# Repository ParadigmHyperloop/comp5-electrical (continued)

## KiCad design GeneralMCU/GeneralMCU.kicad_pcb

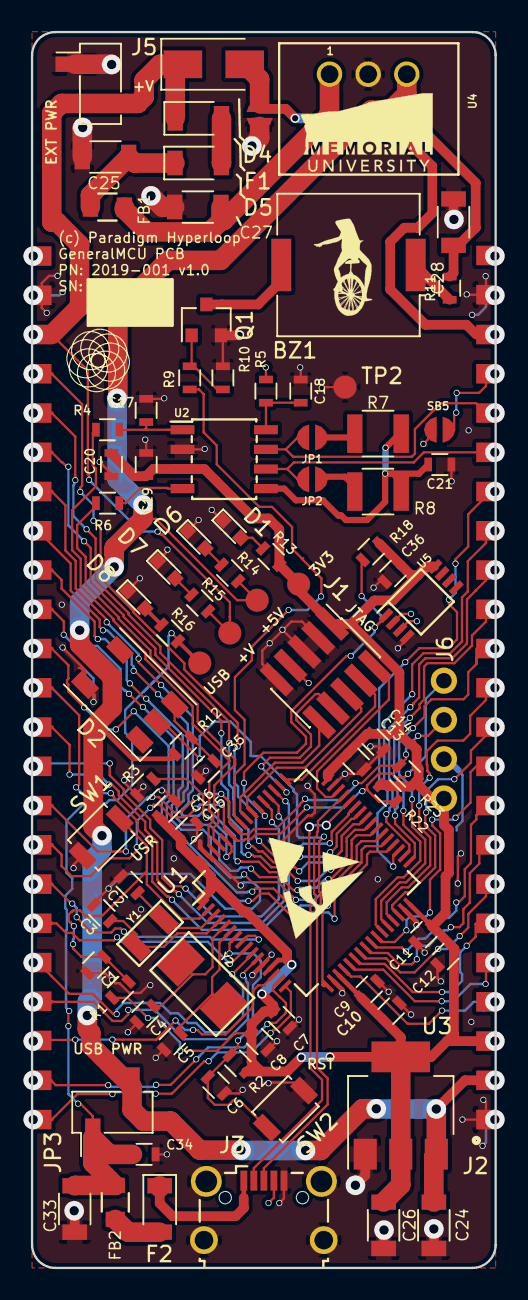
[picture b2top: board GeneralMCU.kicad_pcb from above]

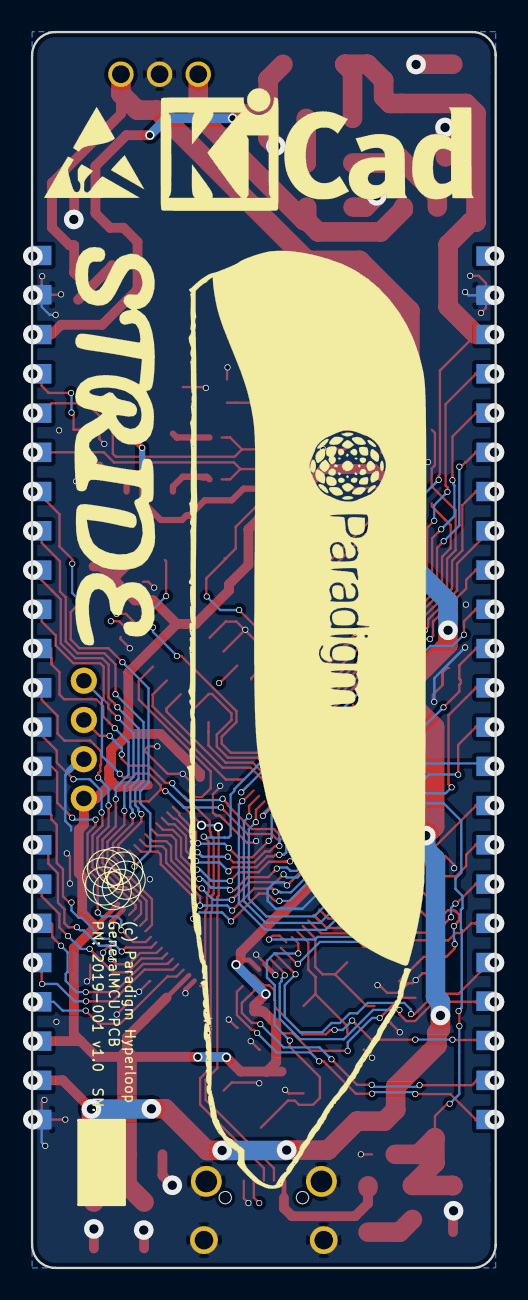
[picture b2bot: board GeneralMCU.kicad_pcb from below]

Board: 2 copper layers, 30.0 x 80.0 mm, 97 parts (6 on the bottom side), 81 nets.

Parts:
BZ1: Buzzer; Buzzer_Murata_PKMCS0909E4000-R1
C1, C6, C7, C9, C11, C13, C15, C18, C19, C36: 0.1u; SMD_pkg_0603
C2, C3: 13p; SMD_pkg_0603
C4, C5: 8p; SMD_pkg_0603
C8: 10n; SMD_pkg_0603
C10, C12, C14, C16, C20, C34, C35: 1u; SMD_pkg_0603
C17: DNP; SMD_pkg_0603
C21: 4.7n; SMD_pkg_0603
C24, C26: 1u; SMD_pkg_1206
C25, C27, C33: 10u; SMD_pkg_1206
C28: 22u; SMD_pkg_1206
D1: 3V3; LED_0603
D2: WS2812B; LED_WS2812-PLCC6
D4: D_TVS; D_SMA
D5: 40V 1A; D_1206
D6: 5V; LED_0603
D7: +V; LED_0603
D8: USB; LED_0603
F1: 3VDC 1A PTC; D_1206
F2: 500mA PTC; D_1206
FB1, FB2: FB; SMD_pkg_0805
J1: ARM_JTAG_SWD; PinHeader_2x05_P1.27mm_Vertical_SMD
J2: SMD46 castellation PKG; PAD42
J3: USB_B_Micro; USB_Micro-B_Wuerth-629105150521_CircularHoles
J5: PWR; Pin_Header_Straight_1x02_Pitch2.54mm_SMD_Pin1Left
J6: OLED; I2C_OLED
JP1, JP2: Jumper_NC_Small; JUMPER_EGG
JP3: Jumper_NC_Small; Pin_Header_Straight_1x02_Pitch2.54mm_SMD_Pin1Left
Q1: Q_NMOS_DGS; SOT-23
R1, R2, R3, R12, R13, R14, R15, R16: 10k; SMD_pkg_0603
R4, R6, R11: 0; SMD_pkg_0603
R5: DNP; SMD_pkg_0603
R7, R8: 60; SMD_pkg_1210
R9, R10: 1k; SMD_pkg_0603
R18, R22, R23: 4.7k; SMD_pkg_0603
SB5, SB6: Jumper_NC_Small; JUMPER_EGG
SW1: USER; SW_SPST_B3U-1000P
SW2: RESET; SW_SPST_B3U-1000P
TP1: 3V3; Measurement_Point_Round-SMD-Pad_Small
TP2: GND; Measurement_Point_Round-SMD-Pad_Small
TP3: 5V; Measurement_Point_Round-SMD-Pad_Small
TP5: +V; Measurement_Point_Round-SMD-Pad_Small
TP6: USB; Measurement_Point_Round-SMD-Pad_Small
U1: STM32F303R6Tx; LQFP-64_10x10mm_Pitch0.5mm
U2: SN65HVD230; SOIC-8_N
U3: AZ1117-3.3; SOT-223-3_TabPin2
U4: P78E05-1000; Recom_INNOLINE-R-78E
U5: DS18B20; MSOP-8
Y1: 32.768kHz; Crystal_NDK_NX3215SA
Y2: 8MHz; Crystal_L5_W3.2
snblock1, snblock2: Logo_Open_Hardware_Small; SN_BLOCK
snblock3, snblock8: Logo_Open_Hardware_Small; Paradigm_Logo_Very_Small
snblock4: Logo_Open_Hardware_Small; poddy
snblock5: Logo_Open_Hardware_Small; KiCad-Logo_8mm_SilkScreen
snblock6, snblock7: Logo_Open_Hardware_Small; ESD-Logo_6.6x6mm_SilkScreen
snblock9: Logo_Open_Hardware_Small; datboi
snblock10: Logo_Open_Hardware_Small; stride
snblock11: Logo_Open_Hardware_Small; MUN

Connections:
+3V3: C7.1, C8.1, C9.1, C10.1, C11.1, C12.1, C13.1, C14.1, C15.1, C16.1, C19.1, C20.1, C26.1, C36.2, J1.1, J2.3, J6.1, R1.2, R2.2, R13.2, R18.2, R22.2, R23.2, TP1.1, U1.1, U1.13, U1.19, U1.32, U1.48, U1.64, U2.3, U3.2, U5.8
+5V: C24.1, C28.1, D2.5, J2.2, JP3.2, R11.2, R12.2, R14.2, TP3.1, U3.3, U4.3
+V: D4.1, F1.1, J2.26, J5.2, R15.2, TP5.1
/BOOT0: R3.2, U1.60
/BUZZ: R9.1, U1.57
/CANH: J2.19, JP1.2, U2.7
/CANL: J2.18, JP2.2, U2.6
/CAN_RX: R6.1, U1.61
/CAN_Shield: J2.20, SB5.1
/CAN_TX: R4.1, U1.62
/I2C1_SCL: J2.38, J6.3, R23.1, U1.58
/I2C1_SDA: J2.39, J6.4, R22.1, U1.59
/JTAG_JTDI: J1.8, U1.50
/JTAG_JTDO: J1.6, U1.55
/JTAG_NJTRST: J1.10, U1.56
/JTAG_SWDCLK\TCK: J1.4, U1.49
/JTAG_SWDIO\TMS: J1.2, U1.46
/NRST: C6.1, R2.1, SW2.2, U1.7
/OSC32_IN: C2.1, U1.3, Y1.1
/OSC32_OUT: C3.1, U1.4, Y1.2
/OSC_IN: C4.1, U1.5, Y2.1
/OSC_OUT: C5.1, U1.6, Y2.2
/PA0: J2.44, U1.14
/PA1: J2.45, U1.15
/PA2: J2.46, U1.16
/PA4: J2.4, U1.20
/PA5: J2.5, U1.21
/PA6: J2.6, U1.22
/PA7: J2.7, U1.23
/PA8: J2.29, U1.41
/PA9: J2.28, U1.42
/PA10: J2.27, U1.43
/PB0: J2.10, U1.26
/PB1: J2.14, U1.27
/PB2: J2.13, U1.28
/PB10: J2.12, U1.29
/PB11: J2.11, U1.30
/PB12: J2.15, U1.33
/PB13: J2.16, U1.34
/PB14: J2.17, U1.35
/PB15: J2.34, U1.36
/PC0: J2.40, U1.8
/PC1: J2.41, U1.9
/PC2: J2.42, U1.10
/PC3: J2.43, U1.11
/PC4: J2.8, U1.24
/PC5: J2.9, U1.25
/PC6: J2.33, U1.37
/PC7: J2.32, U1.38
/PC8: J2.31, U1.39
/PC9: J2.30, U1.40
/PC10: J2.35, U1.51
/PC11: J2.36, U1.52
/PC12: J2.37, U1.53
/PC13: C1.1, R1.1, SW1.2, U1.2
/PD2: R18.1, U1.54, U5.1
/USB_DM: J3.2, U1.44
/USB_DP: J3.3, U1.45
/USR_LED: D2.2, U1.17
/Vref: C21.2, R7.2, R8.1, U2.5
CHASSIS: D4.2, J2.21, SB6.2
GND: C1.2, C2.2, C3.2, C4.2, C5.2, C6.2, C7.2, C8.2, C9.2, C10.2, C11.2, C12.2, C13.2, C14.2, C15.2, C16.2, C17.1, C18.1, C19.2, C20.2, C21.1, C24.2, C25.2, C26.2, C27.2, C28.2, C33.2, C34.2, C35.2, C36.1, D1.1, D2.6, D6.1, D7.1, D8.1, J1.3, J1.5, J1.9, J2.1, J2.22, J2.25, J3.5, J3.6, J5.1, J6.2, Q1.2, R3.1, R10.2, SB5.2, SB6.1, SW1.1, SW2.1, TP2.1, U1.12, U1.18, U1.31, U1.47, U1.63, U2.2, U3.1, U4.2, U5.4
unnamed: BZ1.1, R11.1
unnamed: BZ1.2, Q1.3
unnamed: C17.2, R4.2, U2.1
unnamed: C18.2, R5.1, U2.8
unnamed: C25.1, D5.1, FB1.2
unnamed: C27.1, FB1.1, U4.1
unnamed: C35.1, D2.3, R12.1
unnamed: D1.2, R13.1
unnamed: D5.2, F1.2
unnamed: D6.2, R14.1
unnamed: D7.2, R15.1
unnamed: D8.2, R16.1
unnamed: F2.1, J3.1
unnamed: F2.2, FB2.2
unnamed: JP1.1, R7.1
unnamed: JP2.1, R8.2
unnamed: Q1.1, R9.2, R10.1
unnamed: R6.2, U2.4
VBUS: C33.1, C34.1, FB2.1, JP3.1, R16.2, TP6.1

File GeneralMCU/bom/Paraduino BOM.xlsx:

BOM
Item # | Quantitiy | Value | References | Package | Description | Manufacturer | Manufacturer PN | Supplier | Supplier PN | Unit Cost [$CAD] | Extended [$CAD] | Notes: | Alternates
1.0 | 1.0 | Buzzer | BZ1 | Buzzer_Murata_PKMCS0909E4000-R1 | Buzzer, polarized |  |  | Digi-Key | 490-9647-1-ND |  | 0
2.0 | 10.0 | 0.1u | C1 C6 C7 C9 C11 C13 C15 C18 C19 C36 | SMD_pkg_0603 | Unpolarized capacitor, small symbol |  |  | Digi-Key | 1276-1005-1-ND
3.0 | 1.0 | 10n | C8 | SMD_pkg_0603 | Unpolarized capacitor, small symbol |  |  | Digi-Key | 1276-1926-1-ND
4.0 | 3.0 | 10u | C25 C27 C33 | SMD_pkg_1206 | Unpolarized capacitor, small symbol |  |  | Digi-Key | 1276-6736-1-ND
5.0 | 2.0 | 13p | C2 C3 | SMD_pkg_0603 | Unpolarized capacitor, small symbol |  |  | Digi-Key | 490-1406-1-ND
6.0 | 7.0 | 1u | C10 C12 C14 C16 C20 C34 C35 | SMD_pkg_0603 | Unpolarized capacitor, small symbol |  |  | Digi-Key | 1276-1019-1-ND
7.0 | 2.0 | 1u | C24 C26 | SMD_pkg_1206 | Unpolarized capacitor, small symbol |  |  | Digi-Key | 1276-1068-1-ND
8.0 | 1.0 | 22u | C28 | SMD_pkg_1206 | Unpolarized capacitor, small symbol |  |  | Digi-Key | 1276-6757-1-ND
9.0 | 1.0 | 4.7n | C21 | SMD_pkg_0603 | Unpolarized capacitor, small symbol |  |  | Digi-Key | 399-9091-1-ND
10.0 | 2.0 | 8p | C4 C5 | SMD_pkg_0603 | Unpolarized capacitor, small symbol |  |  | Digi-Key | 1276-1817-1-ND
11.0 | 1.0 | DNP | C17 | SMD_pkg_0603 | Unpolarized capacitor, small symbol |  |  | Digi-Key | ~
13.0 | 4.0 | 3V3 +V 5V USB | D1 | LED_0603 | Light emitting diode |  |  | Digi-Key | 732-4966-1-ND
14.0 | 1.0 | 40V 1A | D5 | D_1206 | Schottky diode, small symbol, filled shape |  |  | Digi-Key | 478-7805-1-ND
16.0 | 1.0 | D_TVS | D4 | D_SMA | Bidirectional transient-voltage-suppression diode |  |  | Digi-Key | SMAJ30ALFCT-ND | *
18.0 | 1.0 | WS2812B | D2 | LED_WS2812-PLCC6 | RGB LED with integrated controller |  |  | Digi-Key | 1568-1800-ND
19.0 | 1.0 | 32VDC 1A PTC | F1 | D_1206 | Fuse, small symbol |  |  | Digi-Key | 507-1801-1-ND
20.0 | 1.0 | 500mA 5V PTC | F2 | D_1206 | Fuse, small symbol |  |  | Digi-Key | 507-1813-1-ND
21.0 | 2.0 | FB | FB1 FB2 | SMD_pkg_0805 | Ferrite bead, small symbol |  |  | Digi-Key | 732-1620-1-ND
22.0 | 1.0 | ARM_JTAG_SWD | J1 | PinHeader_2x05_P1.27mm_Vertical_SMD | Cortex Debug Connector, standard ARM Cortex-M SWD and JTAG interface |  |  | Digi-Key | 609-6529-ND | http://infocenter.arm.com/help/topic/com.arm.doc.faqs/attach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
23.0 | 1.0 | OLED | J6 | I2C_OLED | Generic connector, single row, 01x04, script generated (kicad-library-utils/sch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 |  |  | Digi-Key | S7002-ND
24.0 | 1.0 | USB_B_Micro | J3 | USB_Micro-B_Wuerth-629105150521_CircularHoles | USB Micro Type B connector |  |  | Digi-Key | 609-4616-1-ND
25.0 | 3.0 | Jumper_NC_Small | JP1 JP2 JP3 J5 | Pin_Header_Straight_1x02_Pitch2.54mm_SMD_Pin1Left | Jumper, normally closed, small symbol |  |  | Digi-Key | 952-1913-ND
26.0 | 3.0 | Jumper_NC_Small | JP1 JP2 JP3 | Pin Jumper |  |  |  | Digi-Key | S9337-ND
27.0 | 1.0 | Q_NMOS_DGS | Q1 | SOT-23 | N-MOSFET transistor, gate/source/drain |  |  | Digi-Key | ZXM61N03FCT-ND
28.0 | 5.0 | 0.0 | R4 R6 R11 R20 R21 | SMD_pkg_0603 | Resistor, small US symbol |  |  | Digi-Key | 311-0.0GRCT-ND
29.0 | 8.0 | 10k | R1 R2 R3 R12 R13 R14 R15 R16 | SMD_pkg_0603 | Resistor, small US symbol |  |  | Digi-Key | RNCP0603FTD10K0CT-ND
30.0 | 2.0 | 1k | R9 R10 | SMD_pkg_0603 | Resistor, small US symbol |  |  | Digi-Key | RNCP0603FTD1K00CT-ND
31.0 | 3.0 | 4.7k | R18 R22 R23 | SMD_pkg_0603 | Resistor, small US symbol |  |  | Digi-Key | MCT0603-4.70K-CFCT-ND
32.0 | 2.0 | 60.0 | R7 R8 | SMD_pkg_1210 | Resistor, small US symbol |  |  | Digi-Key | 541-0.0VCT-ND
33.0 | 1.0 | DNP | R5 | SMD_pkg_0603 | Resistor, small US symbol |  |  | Digi-Key | ~
34.0 | 2.0 | RESET, USER | SW1 SW2 | SW_SPST_B3U-1000P | Push button switch, generic, two pins |  |  | Digi-Key | SW1020CT-ND
36.0 | 1.0 | AZ1117-3.3 | U3 | SOT-223-3_TabPin2 | 1A 20V Fixed LDO Linear Regulator, 1.2V, SOT-89/SOT-223/TO-220/TO-252/TO-263 |  |  | Digi-Key | AZ1117EH-3.3TRG1DICT-ND
37.0 | 1.0 | DS18B20 | U5 | MSOP-8 | Programmable Resolution 1-Wire Digital Thermometer MSOP-8 |  |  | Digi-Key | DS18B20U+T&RCT-ND | http://datasheets.maximintegrated.com/en/ds/DS18B20.pdf
38.0 | 1.0 | P78E05-1000 | U4 | Recom_INNOLINE-R-78E |  |  |  | Digi-Key | 102-5018-ND
39.0 | 1.0 | SN65HVD230 | U2 | SOIC-8_N | CAN Bus Transceivers, 3.3V, 1Mbps, Low-Power capabilities, SOIC |  |  | Digi-Key | 296-11654-1-ND | http://www.ti.com/lit/ds/symlink/sn65hvd230.pdf
40.0 | 1.0 | STM32F303R6Tx | U1 | LQFP-64_10x10mm_Pitch0.5mm | ARM Cortex-M4 MCU, 32KB flash, 12KB RAM, 72MHz, 2-3.6V, 51 GPIO, LQFP-64 |  |  | Digi-Key | 497-15163-ND | http://www.st.com/st-web-ui/static/active/en/resource/techni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
41.0 | 1.0 | 32.768kHz | Y1 | Crystal_NDK_NX3215SA | Two pin crystal, small symbol |  |  | Digi-Key | 644-1159-1-ND
42.0 | 1.0 | 8MHz | Y2 | Crystal_L5_W3.2 | Two pin crystal, small symbol |  |  | Digi-Key | 887-1667-1-ND
43.0 | 2.0 |  | J2 | 23 pin tht conn |  |  |  |  | S1012EC-23-ND
 |  |  |  |  |  |  |  |  |  | 1528-2009-ND
 |  |  |  |  |  |  |  | ~ | 49.44

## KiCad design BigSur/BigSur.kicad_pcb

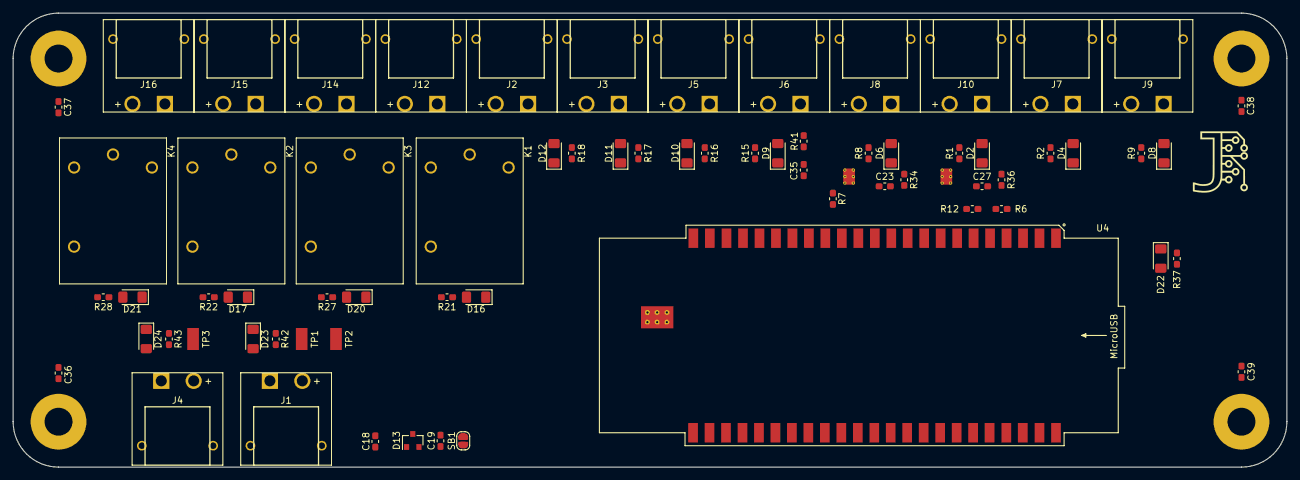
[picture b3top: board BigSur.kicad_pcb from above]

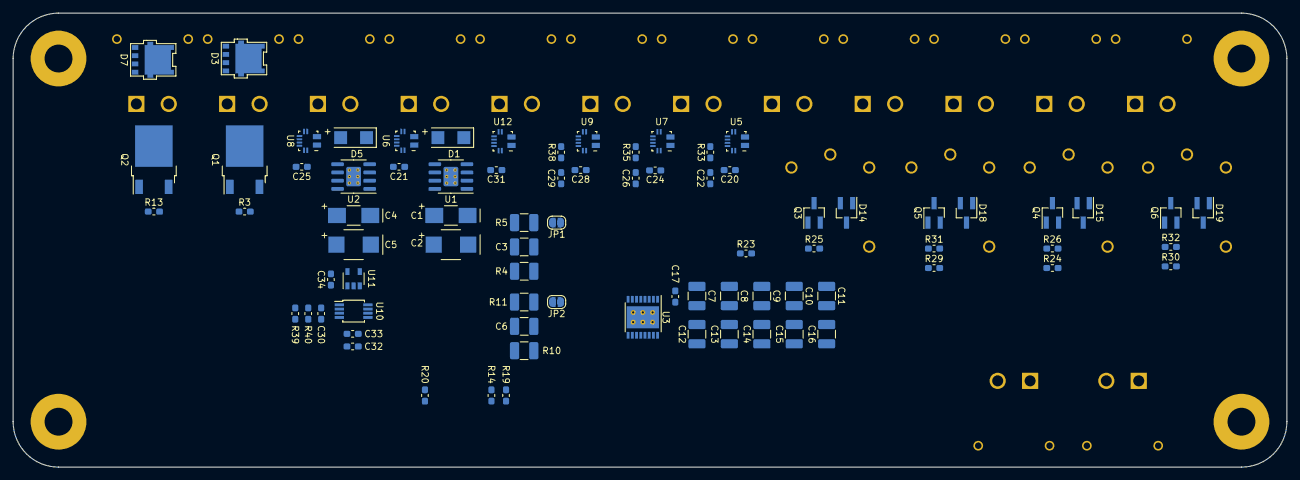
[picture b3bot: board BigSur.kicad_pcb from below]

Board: 2 copper layers, 196.4 x 70.0 mm, 152 parts (79 on the bottom side), 98 nets, no tracks yet.

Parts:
C1, C4: 1uF; KEMET_CAP_SMD_T491C105K050AT
C2, C5: 10uF; VISHAY_CAP_SMD_293D106X9050E2TE3
C3, C6: C; C_1210_3225Metric_Pad1.42x2.65mm_HandSolder
C7, C8, C9, C10, C11, C12, C13, C14, C15, C16: 10uF; C_1210_3225Metric_Pad1.42x2.65mm_HandSolder
C17, C18, C19, C20, C21, C22, C23, C24, C25, C26, C27, C28, C29, C30, C31, C33, C34, C35: 0.1uF; C_0603_1608Metric_Pad1.05x0.95mm_HandSolder
C32: 2.2uF; C_0603_1608Metric_Pad1.05x0.95mm_HandSolder
C36, C37, C38, C39: C; C_0603_1608Metric_Pad1.05x0.95mm_HandSolder
D1, D5: NRVTSA4100E; ONSemi_SMD_Schottky_NRVTSA4100E
D2, D4, D6, D8, D9, D10, D11, D12, D16, D17, D20, D21, D22, D23, D24: QTLP651C4TR; LED_1206_3216Metric_Pad1.42x1.75mm_HandSolder
D3, D7: NTS12120EMFST1G; ONSemi_SMD_Schottky_NTS12120EMFS
D13: NUP2105L; SOT-23
D14, D15, D18, D19: BAS16LT1G; SOT-23_Handsoldering
H1, H2, H3, H4: Hole; MountingHole_4.3mm_M4_Pad
J1, J2, J3, J4, J5, J6, J7, J8, J9, J10, J12, J14, J15, J16: XT30PW-M; AMASS_XT30PW-M
JP1, JP2: Jumper; SolderJumper-2_P1.3mm_Open_RoundedPad1.0x1.5mm
K1, K2, K3, K4: G5LE-1A-VDDC12; OMRON_RELAY_G5LE-1A-VDDC12
Q1, Q2: TSM900N10; TO-252-2
Q3, Q4, Q5, Q6: MMBT3904-7-F; SOT-23_Handsoldering
R1, R2, R8, R9, R15, R16, R17, R18, R21, R22, R27, R28, R37: 68; R_0603_1608Metric_Pad1.05x0.95mm_HandSolder
R3, R6, R7, R12, R13, R19, R20, R25, R26, R31, R32, R33, R34, R35, R36, R38, R39, R41: 10K; R_0603_1608Metric_Pad1.05x0.95mm_HandSolder
R4, R5, R10, R11: R_US; R_1210_3225Metric_Pad1.42x2.65mm_HandSolder
R14: 5.1K; R_0603_1608Metric_Pad1.05x0.95mm_HandSolder
R23, R24, R29, R30, R43: 1K; R_0603_1608Metric_Pad1.05x0.95mm_HandSolder
R40: 1.1K; R_0603_1608Metric_Pad1.05x0.95mm_HandSolder
R42: 2K; R_0603_1608Metric_Pad1.05x0.95mm_HandSolder
SB1: Jumper_NC_Small; SolderJumper-2_P1.3mm_Open_RoundedPad1.0x1.5mm
TP1, TP2, TP3: 5015; Keystone_TP_SMD_5015
U1, U2: DRV103H; SOIC-8-1EP_3.9x4.9mm_P1.27mm_EP2.29x3mm_ThermalVias
U3: DRV8806; HTSSOP-16-1EP_4.4x5mm_P0.65mm_EP3.4x5mm_Mask2.46x2.31mm_The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
U4: SMD46; SMD42-FTP
U5, U6, U7, U8, U9, U12: ACS70331EESATR-2P5U3; Allegro_QFN_ACS70331EESATR
U10: MCP6L02T-E_MS; MSOP-8_3x3mm_P0.65mm
U11: 74LVC1G00W5-7; SOT-23-5

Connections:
+3V3: C20.1, C21.1, C24.1, C25.1, C28.1, C31.1, C32.1, C33.1, C34.1, R1.2, R2.1, R7.1, R8.2, R9.1, R15.1, R16.1, R17.1, R18.1, R20.1, R21.1, R22.1, R27.1, R28.1, R39.1, U4.3, U5.12, U6.12, U7.12, U8.12, U9.12, U10.8, U11.5, U12.12
+12V: D14.1, D15.1, D18.1, D19.1, D24.2, J4.2, K1.2, K2.2, K3.2, K4.2, TP3.1
+24V: C1.1, C2.1, C4.1, C5.1, C7.1, C8.1, C9.1, C10.1, C11.1, C12.1, C13.1, C14.1, C15.1, C16.1, C17.1, D1.1, D3.1, D5.1, D7.1, D23.2, J1.2, J2.2, J3.2, J5.2, J6.2, J7.2, J8.2, J9.2, J10.2, TP1.1, U1.6, U2.6, U3.1, U3.2, U4.26
/SolenoidSense/SOLENOID_OFF_VREF: C30.1, R39.2, R40.1, U10.2, U10.6
BRAKE_SOLENOID_HIGH: R37.1, U11.4
CAN_H: C18.1, D13.1, U4.19
CAN_L: C19.2, D13.2, U4.18
CAN_SHIELD: SB1.2, U4.20
DRV103_DUTY_CYCLE_ADJ_1: JP1.1, U4.4
DRV103_DUTY_CYCLE_ADJ_2: JP2.1, U4.5
DRV103_INPUT_1: R6.1, U1.8, U4.27
DRV103_INPUT_2: R12.1, U2.8, U4.28
DRV103_nOK: R7.2, U1.7, U2.7, U4.37
DRV8806_RESET: U3.9, U4.29
DRV8806_SERIAL_CLK: U3.13, U4.33
DRV8806_SERIAL_DATIN: U3.14, U4.32
DRV8806_SERIAL_DATOUT: R14.1, U3.15
DRV8806_SERIAL_DATOUT_3.3V: R14.2, R19.1, U4.31
DRV8806_SERIAL_LATCH: U3.11, U4.34
DRV8806_nENBL: U3.8, U4.30
DRV8806_nFAULT: R20.2, U3.16, U4.35
GND: C1.2, C2.2, C3.2, C4.2, C5.2, C6.2, C7.2, C8.2, C9.2, C10.2, C11.2, C12.2, C13.2, C14.2, C15.2, C16.2, C17.2, C18.2, C19.1, C20.2, C21.2, C22.2, C23.2, C24.2, C25.2, C26.2, C27.2, C28.2, C29.2, C30.2, C31.2, C32.2, C33.2, C34.2, C35.2, D13.3, D22.1, J1.1, J4.1, Q1.3, Q2.3, Q3.2, Q4.2, Q5.2, Q6.2, R3.2, R4.2, R5.2, R6.2, R10.2, R11.2, R12.2, R13.2, R19.2, R25.2, R26.2, R31.2, R32.2, R40.2, R42.2, R43.2, SB1.1, TP2.1, U1.4, U1.9, U2.4, U2.9, U3.5, U3.12, U3.17, U4.1, U4.22, U4.25, U5.5, U5.6, U5.8, U5.9, U5.11, U6.5, U6.6, U6.8, U6.9, U6.11, U7.5, U7.6, U7.8, U7.9, U7.11, U8.5, U8.6, U8.8, U8.9, U8.11, U9.5, U9.6, U9.8, U9.9, U9.11, U10.4, U11.3, U12.5, U12.6, U12.8, U12.9, U12.11
GNDPWR: C36.2, C37.2, C38.2, C39.2, U4.21
GP_RELAY_1: R23.2, U4.12
GP_RELAY_1_HIGH: J12.2, K1.3
GP_RELAY_1_LOW: J12.1, K1.1
GP_RELAY_2: R29.2, U4.13
GP_RELAY_2_HIGH: J14.2, K3.3
GP_RELAY_2_LOW: J14.1, K3.1
GP_RELAY_3: R24.2, U4.14
GP_RELAY_3_HIGH: J15.2, K2.3
GP_RELAY_3_LOW: J15.1, K2.1
GP_RELAY_4: R30.2, U4.15
GP_RELAY_4_HIGH: J16.2, K4.3
GP_RELAY_4_LOW: J16.1, K4.1
unnamed: C3.1, U1.2
unnamed: C6.1, U2.2
unnamed: C36.1, H1.1
unnamed: C37.1, H2.1
unnamed: C38.1, H3.1
unnamed: C39.1, H4.1
unnamed: D2.2, R1.1
unnamed: D4.2, R2.2
unnamed: D6.2, R8.1
unnamed: D8.2, R9.2
unnamed: D9.2, R15.2
unnamed: D10.2, R16.2
unnamed: D11.2, R17.2
unnamed: D12.2, R18.2
unnamed: D14.2, D16.1, K1.5, Q3.3
unnamed: D15.2, D17.1, K2.5, Q4.3
unnamed: D16.2, R21.2
unnamed: D17.2, R22.2
unnamed: D18.2, D20.1, K3.5, Q5.3
unnamed: D19.2, D21.1, K4.5, Q6.3
unnamed: D20.2, R27.2
unnamed: D21.2, R28.2
unnamed: D22.2, R37.2
unnamed: D23.1, R42.1
unnamed: D24.1, R43.1
unnamed: JP1.2, R4.1, U1.1
unnamed: JP2.2, R10.1, U2.1
unnamed: Q3.1, R23.1, R25.1
unnamed: Q4.1, R24.1, R26.1
unnamed: Q5.1, R29.1, R31.1
unnamed: Q6.1, R30.1, R32.1
unnamed: R5.1, U1.3
unnamed: R11.1, U2.3
unnamed: R33.2, U5.10
unnamed: R34.2, U6.10
unnamed: R35.2, U7.10
unnamed: R36.2, U8.10
unnamed: R38.2, U9.10
unnamed: R41.2, U12.10
unnamed: U10.1, U11.1
unnamed: U10.7, U11.2
PUMP_INPUT_1: Q1.1, R3.1, U4.17
PUMP_INPUT_2: Q2.1, R13.1, U4.16
PUMP_LS_CHANNEL_1: D3.2, D4.1, J7.1, Q1.2
PUMP_LS_CHANNEL_2: D7.2, D8.1, J9.1, Q2.2
SOLENOID_CURRENT_SENSE_1: C22.1, R33.1, U4.44
SOLENOID_CURRENT_SENSE_2: C26.1, R35.1, U4.45
SOLENOID_CURRENT_SENSE_3: C29.1, R38.1, U4.46
SOLENOID_CURRENT_SENSE_4: C35.1, R41.1, U4.6
SOLENOID_ECONOMIZED_CHANNEL_1: J8.1, U6.3
SOLENOID_ECONOMIZED_CHANNEL_1_SENSE: D1.2, D2.1, U1.5, U6.1
SOLENOID_ECONOMIZED_CHANNEL_2: J10.1, U8.3
SOLENOID_ECONOMIZED_CHANNEL_2_SENSE: D5.2, D6.1, U2.5, U8.1
SOLENOID_ECONOMIZED_CURRENT_SENSE_1: C23.1, R34.1, U4.7, U10.3
SOLENOID_ECONOMIZED_CURRENT_SENSE_2: C27.1, R36.1, U4.8, U10.5
SOLENOID_LS_CHANNEL_1: J2.1, U5.3
SOLENOID_LS_CHANNEL_1_SENSE: D12.1, U3.3, U5.1
SOLENOID_LS_CHANNEL_2: J3.1, U7.3
SOLENOID_LS_CHANNEL_2_SENSE: D11.1, U3.4, U7.1
SOLENOID_LS_CHANNEL_3: J5.1, U9.3
SOLENOID_LS_CHANNEL_3_SENSE: D10.1, U3.6, U9.1
SOLENOID_LS_CHANNEL_4: J6.1, U12.3
SOLENOID_LS_CHANNEL_4_SENSE: D9.1, U3.7, U12.1

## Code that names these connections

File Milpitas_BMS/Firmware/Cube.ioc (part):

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Mcu.Name=STM32F303R(D-E)Tx
Mcu.Package=LQFP64
Mcu.UserName=STM32F303RETx
PA0.GPIOParameters=GPIO_Label
PA0.GPIO_Label=I_DIS
PA0.Mode=IN1-Single-Ended
PA0.Signal=ADC1_IN1
PA1.GPIOParameters=GPIO_Label
PA1.GPIO_Label=V_DIS
PA1.Mode=IN2-Single-Ended
PA1.Signal=ADC1_IN2
PA10.GPIOParameters=GPIO_Label
PA10.GPIO_Label=SM1_OUTPUT
PA10.Signal=GPIO_Output
PA11.Mode=Master
PA11.Signal=CAN_RX
PA12.Mode=Master
PA12.Signal=CAN_TX
PA13.Mode=JTAG_5_pins
PA13.Signal=SYS_JTMS-SWDIO
PA14.Mode=JTAG_5_pins
PA14.Signal=SYS_JTCK-SWCLK
PA15.Mode=JTAG_5_pins
PA15.Signal=SYS_JTDI
PA2.GPIOParameters=GPIO_Label
PA2.GPIO_Label=I_BATT
PA2.Mode=IN3-Single-Ended
PA2.Signal=ADC1_IN3
PA3.GPIOParameters=GPIO_Label
PA3.GPIO_Label=V_BATT
PA3.Mode=IN4-Single-Ended
PA3.Signal=ADC1_IN4
PA8.GPIOParameters=GPIO_Label
PA8.GPIO_Label=DIS_LED
PA8.Signal=GPIO_Output
PA9.GPIOParameters=GPIO_Label
PA9.GPIO_Label=SM0_LED
PA9.Signal=GPIO_Output
PB0.GPIOParameters=GPIO_Label
PB0.GPIO_Label=USER_BUTTON
PB0.Signal=GPIO_Input
PB1.GPIOParameters=GPIO_Label
PB1.GPIO_Label=BMS_WAKE_N
PB1.Signal=GPIO_Output
PB10.GPIOParameters=GPIO_Label
PB10.GPIO_Label=BMS_UART_N
PB10.Mode=Asynchronous
PB10.Signal=USART3_TX
PB11.GPIOParameters=GPIO_Label
PB11.GPIO_Label=BMS_UART_P
PB11.Mode=Asynchronous
PB11.Signal=USART3_RX
PB3.Mode=JTAG_5_pins
PB3.Signal=SYS_JTDO-TRACESWO
PB4.Mode=JTAG_5_pins
PB4.Signal=SYS_NJTRST
PB5.GPIOParameters=GPIO_Label
PB5.GPIO_Label=CHG_ON
PB5.Signal=GPIO_Output
PB6.GPIOParameters=GPIO_Label
PB6.GPIO_Label=CHG_FAULT
PB6.Signal=GPXTI6
PC0.GPIOParameters=GPIO_Label
PC0.GPIO_Label=I_CHG
PC0.Signal=ADCx_IN6
PC1.GPIOParameters=GPIO_Label
PC1.GPIO_Label=V_CHG
PC1.Signal=ADCx_IN7
PC10.GPIOParameters=GPIO_Label
PC10.GPIO_Label=BATT_ON
PC10.Signal=GPIO_Output
PC11.GPIOParameters=GPIO_Label
PC11.GPIO_Label=BATT_FAULT
PC11.Signal=GPXTI11
PC12.GPIOParameters=GPIO_Label
PC12.GPIO_Label=DIS_ON
PC12.Signal=GPIO_Output
PC14-OSC32_IN.Mode=LSE-External-Oscillator
PC14-OSC32_IN.Signal=RCC_OSC32_IN
PC15-OSC32_OUT.Mode=LSE-External-Oscillator
PC15-OSC32_OUT.Signal=RCC_OSC32_OUT
PC4.GPIOParameters=GPIO_Label
PC4.GPIO_Label=DIAGS_P
PC4.Mode=Asynchronous
PC4.Signal=USART1_TX
PC5.GPIOParameters=GPIO_Label
PC5.GPIO_Label=DIAGS_N
PC5.Mode=Asynchronous
PC5.Signal=USART1_RX
PC8.GPIOParameters=GPIO_Label
PC8.GPIO_Label=BATT_LED
PC8.Signal=GPIO_Analog
PC9.GPIOParameters=GPIO_Label
PC9.GPIO_Label=CHG_LED
PC9.Signal=GPIO_Output
PD2.GPIOParameters=GPIO_Label
PD2.GPIO_Label=DIS_FAULT
PD2.Signal=GPXTI2
PF0-OSC_IN.Mode=HSE-External-Oscillator
PF0-OSC_IN.Signal=RCC_OSC_IN
PF1-OSC_OUT.Mode=HSE-External-Oscillator
PF1-OSC_OUT.Signal=RCC_OSC_OUT
RCC.HSE_VALUE=16000000
RCC.SYSCLKFreq_VALUE=8000000
board=custom

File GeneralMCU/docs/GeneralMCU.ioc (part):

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Mcu.Name=STM32F303R(D-E)Tx
Mcu.Package=LQFP64
Mcu.UserName=STM32F303RETx
PA0.Mode=IN1-Single-Ended
PA0.Signal=ADC1_IN1
PA11.Mode=Device
PA11.Signal=USB_DM
PA12.Mode=Device
PA12.Signal=USB_DP
PA13.GPIOParameters=GPIO_Label
PA13.GPIO_Label=TMS
PA13.Mode=JTAG_5_pins
PA13.Signal=SYS_JTMS-SWDIO
PA14.GPIOParameters=GPIO_Label
PA14.GPIO_Label=TCK
PA14.Mode=JTAG_5_pins
PA14.Signal=SYS_JTCK-SWCLK
PA15.Mode=JTAG_5_pins
PA15.Signal=SYS_JTDI
PA2.GPIOParameters=GPIO_Speed,GPIO_PuPd,GPIO_Label,GPIO_Mode
PA2.GPIO_Label=USART_TX
PA2.GPIO_Mode=GPIO_MODE_AF_PP
PA2.GPIO_PuPd=GPIO_NOPULL
PA2.GPIO_Speed=GPIO_SPEED_FREQ_LOW
PA2.Mode=Asynchronous
PA2.Signal=USART2_TX
PA3.GPIOParameters=GPIO_Speed,GPIO_PuPd,GPIO_Label,GPIO_Mode
PA3.GPIO_Label=USART_RX
PA3.GPIO_Mode=GPIO_MODE_AF_PP
PA3.GPIO_PuPd=GPIO_NOPULL
PA3.GPIO_Speed=GPIO_SPEED_FREQ_LOW
PA3.Mode=Asynchronous
PA3.Signal=USART2_RX
PA4.Signal=COMP_DAC11_group
PA5.GPIOParameters=GPIO_Speed,GPIO_PuPd,GPIO_Label,GPIO_Mode
PA5.GPIO_Label=LD2 [Green Led]
PA5.GPIO_Mode=GPIO_MODE_OUTPUT_PP
PA5.GPIO_PuPd=GPIO_NOPULL
PA5.GPIO_Speed=GPIO_SPEED_FREQ_LOW
PA5.Signal=GPIO_Output
PB13.Mode=Full_Duplex_Master
PB13.Signal=SPI2_SCK
PB14.Mode=Full_Duplex_Master
PB14.Signal=SPI2_MISO
PB15.Mode=Full_Duplex_Master
PB15.Signal=SPI2_MOSI
PB3.Mode=JTAG_5_pins
PB3.Signal=SYS_JTDO-TRACESWO
PB4.Mode=JTAG_5_pins
PB4.Signal=SYS_NJTRST
PB6.Mode=I2C
PB6.Signal=I2C1_SCL
PB7.Mode=I2C
PB7.Signal=I2C1_SDA
PB8.Mode=Master
PB8.Signal=CAN_RX
PB9.Mode=Master
PB9.Signal=CAN_TX
PC13.GPIOParameters=GPIO_Label,GPIO_ModeDefaultEXTI
PC13.GPIO_Label=B1 [Blue PushButton]
PC13.GPIO_ModeDefaultEXTI=GPIO_MODE_IT_FALLING
PC13.Signal=GPXTI13
PC14-OSC32_IN.Mode=LSE-External-Oscillator
PC14-OSC32_IN.Signal=RCC_OSC32_IN
PC15-OSC32_OUT.Mode=LSE-External-Oscillator
PC15-OSC32_OUT.Signal=RCC_OSC32_OUT
PF0-OSC_IN.Mode=HSE-External-Oscillator
PF0-OSC_IN.Signal=RCC_OSC_IN
PF1-OSC_OUT.Mode=HSE-External-Oscillator
PF1-OSC_OUT.Signal=RCC_OSC_OUT
RCC.HSE_VALUE=8000000
RCC.SYSCLKFreq_VALUE=48000000
RCC.SYSCLKSourceVirtual=RCC_SYSCLKSOURCE_PLLCLK
board=NUCLEO-F303RE
boardIOC=true

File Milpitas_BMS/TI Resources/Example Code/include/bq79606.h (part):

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#define OTUT_CTRL				0x2C // GPIO over and under temperature comparator control
#define OTUT_THRESH				0x2D // GPIO comparator over and under temperature threshold
#define COMP_DG					0x2E // Comparator protection deglitch
#define GPIO1_CONF				0x2F // GPIO1 configuration
#define GPIO2_CONF				0x30 // GPIO2 configuration
#define GPIO3_CONF				0x31 // GPIO3 configuration
#define GPIO4_CONF				0x32 // GPIO4 configuration
#define GPIO5_CONF				0x33 // GPIO5 configuration
#define GPIO6_CONF				0x34 // GPIO6 configuration
#define CELL1_GAIN				0x35 // Cell 1 gain calibration
#define CELL2_GAIN				0x36 // Cell 2 gain calibration
#define CELL3_GAIN				0x37 // Cell 3 gain calibration
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#define CELL4_OFF				0x3E // Cell 4 offset calibration
#define CELL5_OFF				0x3F // Cell 5 offset calibration
#define CELL6_OFF				0x40 // Cell 6 offset calibration
#define GPIO1_GAIN				0x41 // GPIO1 gain calibration
#define GPIO2_GAIN				0x42 // GPIO2 gain calibration
#define GPIO3_GAIN				0x43 // GPIO3 gain calibration
#define GPIO4_GAIN				0x44 // GPIO4 gain calibration
#define GPIO5_GAIN				0x45 // GPIO5 gain calibration
#define GPIO6_GAIN				0x46 // GPIO6 gain calibration
#define GPIO1_OFF				0x47 // GPIO1 offset calibration
#define GPIO2_OFF				0x48 // GPIO2 offset calibration
#define GPIO3_OFF				0x49 // GPIO3 offset calibration
#define GPIO4_OFF				0x4A // GPIO4 offset calibration
#define GPIO5_OFF				0x4B // GPIO5 offset calibration
#define GPIO6_OFF				0x4C // GPIO6 offset calibration
#define GPAUXCELL_GAIN			0x4D // GP ADC gain, CH1
#define GPAUXCELL_OFF			0x4E // GP ADC offset, CH1
#define GPAUX_GAIN				0x4F // GP ADC gain, CH2-32
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#define AUX_ZEROL				0x22A // ZERO reference voltage low byte                       
#define AUX_AVDDH				0x22B // AVDD LDO voltage output high byte
#define AUX_AVDDL				0x22C // AVDD LDO voltage output low byte             
#define AUX_GPIO1H				0x22D // GPIO1 voltage high byte (corrected)
#define AUX_GPIO1L				0x22E // GPIO1 voltage low byte (corrected)
#define AUX_GPIO2H				0x22F // GPIO2 voltage high byte (corrected)
#define AUX_GPIO2L				0x230 // GPIO2 voltage low byte (corrected)
#define AUX_GPIO3H				0x231 // GPIO3 voltage high byte (corrected)
#define AUX_GPIO3L				0x232 // GPIO3 voltage low byte (corrected)
#define AUX_GPIO4H				0x233 // GPIO4 voltage high byte (corrected)
#define AUX_GPIO4L				0x234 // GPIO4 voltage low byte (corrected)
#define AUX_GPIO5H				0x235 // GPIO5 voltage high byte (corrected)
#define AUX_GPIO5L				0x236 // GPIO5 voltage low byte (corrected)
#define AUX_GPIO6H				0x237 // GPIO6 voltage high byte (corrected)
#define AUX_GPIO6L				0x238 // GPIO6 voltage low byte (corrected)
#define AUX_FACTCORRH			0x239 // Selected GPIO factory corrected high byte
#define AUX_FACTCORRL			0x23A // Selected GPIO factory corrected low byte                       
#define DIE_TEMPH				0x23B // Die junction temperature high byte                       
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#define VCELL6_LU				0x2D1 // Cell 6 voltage low byte (uncorrected)
#define AUX_BAT_HU				0x2D2 // Cell stack voltage high byte (uncorrected)
#define AUX_BAT_LU				0x2D3 // Cell stack voltage low byte (uncorrected)
#define AUX_GPIO1_HU			0x2D4 // GPIO1 voltage high byte (uncorrected)
#define AUX_GPIO1_MU			0x2D5 // GPIO1 voltage middle byte (uncorrected)
#define AUX_GPIO1_LU			0x2D6 // GPIO1 voltage low byte (uncorrected)
#define AUX_GPIO2_HU			0x2D7 // GPIO2 voltage high byte (uncorrected)
#define AUX_GPIO2_LU			0x2D8 // GPIO2 voltage low byte (uncorrected)
#define AUX_GPIO3_HU			0x2D9 // GPIO3 voltage high byte (uncorrected)
#define AUX_GPIO3_LU			0x2DA // GPIO3 voltage low byte (uncorrected)
#define AUX_GPIO4_HU			0x2DB // GPIO4 voltage high byte (uncorrected)
#define AUX_GPIO4_LU			0x2DC // GPIO4 voltage low byte (uncorrected)
#define AUX_GPIO5_HU			0x2DD // GPIO5 voltage high byte (uncorrected)
#define AUX_GPIO5_LU			0x2DE // GPIO5 voltage low byte (uncorrected)
#define AUX_GPIO6_HU			0x2DF // GPIO6 voltage high byte (uncorrected)
#define AUX_GPIO6_LU			0x2E0 // GPIO6 voltage low byte (uncorrected)
#define CUST_CRC_RSLTH			0x2E1 // Calculated customer CRC result high byte                                    
#define CUST_CRC_RSLTL			0x2E2 // Calculated customer CRC result low byte
                  
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
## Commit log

2019-07-24 added License and template folder
2019-07-24 added meme cape sch
2019-07-31 Added stm32cubemx start
    Added cubemx project for f303. needs adc and gpio added
2019-08-11 First commit - brain dump
2019-08-13 Updated some silly mistakes
    Updated some silly mistakes,
    - capacitor decoupled to gnd
    - Added option for jumper control to 2 24V modules
2019-08-13 Plopped mcu onto schematic
    Nothing final here yet besides mcu, other parts will change.
2019-08-14 Schematic getting toasty.
    99% Percent of symbols added with 90% of footprints filled in, 30% of parts spec'd.
    Layout organized by functional group
2019-08-22 Add PodOverview schematic
2019-09-16 Needs castellated pads and sch review
2019-09-16 Initial commit of Big Sur (Actuation Board).
    Solenoid drivers and sense *mostly* complete, pump drivers started.
2019-09-20 Work on pump drivers.
2019-09-23 Started filling in pinout of Paraduino connector, based on current Paraduino schematic.
2019-10-02 Updated current sense, second pump driver, solenoid connectors
    -Current sense now uses current sense ICs, connected to Paraduino ADC pins.
    -Added second pump driver.
    -Connected outputs with XT30 connectors.
    -Still need some Paraduino connections, inverter driver, footprints.
2019-10-03 Removed Inverter
2019-10-05 Schematics Complete
    Still need to spec resistors, and XT30s, then should be ready for layout and routing.
2019-10-05 Changed "Big Sur" to "BigSur" to fit more closely with KiCAD conventions.
2019-10-07 Redid the layout of the board to be better
    Smaller 30x80mm footprint. Sch symbol and footprint for the board can be found under the example folder. Routing needs to be made nice yet.
2019-10-08 Added test points, started CAN connector.
2019-10-08 Can't remember these changes lol
    From the meeting, switching back to branch now.
2019-10-09 Added mounting holes, CAN connector, indicator LEDs, started general purpose relays
2019-10-10 Chose LEDs.
2019-10-11 Fixed castellated pads. Ready for review
2019-10-12 Updated test points
2019-10-13 Added silk and generated gerbers. Review me.
2019-10-13 Updated BOM
2019-10-13 Updated Example project and smd sym and footprint for recieving pcbs.
2019-10-14 Updated input control circuitry. Rationale and calcs in google drive.
    Updated and added all part numbers for input protection circuitry. Not yet ready for review.
2019-10-17 Added braking detection, relay flyback, changed current sensors.
2019-10-17 Added to self deprecation.
2019-10-18 Order time V1.0 locked-in, updated gerbs
2019-10-18 Added indicator LED for braking
2019-10-18 Added inverter kill connectors.
2019-10-18 Cleaned up comments. (sorry for the electrical alerts spam bys)
2019-10-18 PDF export
2019-10-22 Fixed current sense, added GP relay LEDs
2019-10-22 Cleaned up schematics
2019-10-22 Updated Paraduino pinout (again)
2019-10-25 Schematic lost in time, grab later from past commit. Added noncast version because we have no cashhhhhhhh
2019-10-28 Added caps on mounting holes, reversed connector polarity
2019-10-28 XT30 sourcing and footprints
2019-10-28 Switched to active low brake lines
2019-11-03 Generate netlist, started some very rough placement
2019-11-05 Initial layout pass. This will be changed many times I'm sure.
2019-11-05 Moved configuration passives for DRV103s.
2019-11-08 Moved some things.
2019-11-08 More layout changes
2019-11-08 Added power LEDs.
2019-11-11 Added custom 3d models for some parts, continued work on layout.
2019-11-11 created project
    Made initial KiCAD project
2019-11-13 Made brake output active high in accordance with meeting decision
2019-11-14 Moved connectors to fit new LV plate layout
2019-11-19 Squished output connectors together, going to need to fix layout.
    Also still needs CAN and inverter chill connectors.
2019-11-21 Revert "Order time V1.0 locked-in, updated gerbs"
    This reverts commit a2b677ba43e52ec178062c1ac254df27289ef0f4.
2019-11-21 Used sch-bak to recover sch, updated pdf
    -bak sch seemed to be correct so I just used that instead of a past commit.
2019-11-21 Revert "Schematic lost in time, grab later from past commit. Added noncast version because we have no cashhhhhhhh"
    This reverts commit bf9f08a9f085a0130a5e5ccea324bcbd31a22aae.
2019-11-21 Messed Up reverting to wrong branch
    ?Fixed 4 real
2019-11-21 Revert "Messed Up reverting to wrong branch"
    This reverts commit e1d58d906c6809b50785ce825482dcb9b69fc5d2.
2019-11-21 WE BACK BABY
    sorry for tying up master lol
2019-11-21 Adding in old rescued folder.
2019-11-22 started test code
2019-11-25 Fixed braking LED direction
2019-11-29 Finished another layout pass.
2020-03-29 Primary Sch for milpitas BMS eval board
    This board will be used to evaluate whether or not adding BMS functionality to the LV distribution board (Milpitas) would be worth it.
2020-03-30 updated some parts to inclued footprints + digikey P/N
2020-04-03 lots of little fixes
2020-04-04 For review call
2020-04-05 prelim layout ???
2020-04-05 (maybe) final placement V1,0
2020-04-11 First pass routing
2020-04-12 Rearrange file structure. Added silkscreeen stuff
2020-04-12 oops fixed file structure again
2020-04-13 Ordered board. Hopefully it's all gucci prada
2020-05-02 Some firmware work
2020-05-23 Continued work on firmware
2020-05-25 Create general PCB MCU layout (Mojave)
2020-06-08 Merging back in to master
2020-06-08 Update PCB_Mojave to use Hyperlib instead of project specific library
2020-07-16 Export STEP and dimension drawing, preparing to merge with master.
